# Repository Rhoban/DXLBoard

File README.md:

# Rhoban DXL Board

This communication board was designed and used by the Rhoban teams for
humanoid robots. It features:

* 3 separate dynamixel buses that can be used in parallel, compatible with
  both 3-pin and 4-pin
* A socket for a GY-85 IMU
* A socket for a Maple Mini controller (based on the Cortex-M3, 32 bit
  arm at 72Mhz)
* USB cable can be directly soldered on it
* GPIO that can be used for buttons or any other purposes

## Documentation

Here you can find documentation about:

* [Electronics](/electronics/#electronics)
* [Mechanics](/mechanics/#mechanics)
* [Firmware](/firmware/#firmware)

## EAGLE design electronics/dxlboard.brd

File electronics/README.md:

# Electronics

Here you'll find the schematic and (auto)routed board. You will need Eagle
to open the `.sch` and `.brd` files.

## Components

Here is a list of required components to build the board

Name               | Farnell ID | Quantity | Description
-------------------|------------|----------|--------------
2212S-20SG-85      | 1593469    | 2        | 1x20 0.1" female sockets for the Maple Mini
2212S-08SG-85      | 1593463    | 1        | 1x8 0.1" female socket for the IMU
MOLEX 22-03-5045   | 1104204    | 3        | Dynamixel 4 pins connector
MOLEX 22-03-5035   | 9979620    | 3        | Dynamixel 3 pins connector
ST485              | 1564306    | 3        | Buses transciever (can be replaced with MAX485), SOIC-8
R0805 22 ohms      | 2128982    | 8        | Protection resistors
R0805 1.5 Kohms    | 2129125    | 1        | USB detection resistor
R0805 2 Kohms      | 2129135    | 3        | Pull-up/Pull-down
R0805 3 Kohms      | 2129150    | 15       | Pull-up/Pull-down
C0805 100 nF       | 1759265RL  | 3        | Decoupling condensators
PMEG2005AEA        | 8737843RL  | 1        | Diode for on-board USB power supply
Maple mini      | N/A        | 1        | Controller board, featuring a 72Mhz 32-bit Cortex-M3 ARM controller
GY-85           | N/A        | 1        | 9 DOF IMU

## Powering

In the current version, the board is powered using 5V USB. You can use the mini
USB port from the Maple Mini, or solder wires to the USB part of the board (we
recommend doing that to have a better integration). There is protection diode
on the Maple Mini and on the board.

The motor power lines are connected, however the board is not designed to
handle current so you still have to build a separate hub if you want to
power servomotors. 

## Bus design

The ST485 transciever is used here for both RS485 and TTL versions. It can also
be replaced with MAX485 which is pin compatible.

22 ohms serie resistors are used for bus protections to avoid damaging transcivers from
the devices or the board in the case the bus would be driven simultaneously by both.

There is a pull-up on the A line and a the B line is pulled to 2.5V. 

When transmitting, the lines are driven by the ST485, A is the positive output and B
the negative. In this case, the A line acts exactly as the data line of a TTL device.

When receiving, if you are using only 3-pins TTL, the A line will be either 5V (for '1')
or 0V (for '0') and the B line will remain at 2.5V. In this case, the RS485 speficiation
is still respected, because A-B should be above 200mV to read a '1' and below -200mV to
read a '0'.

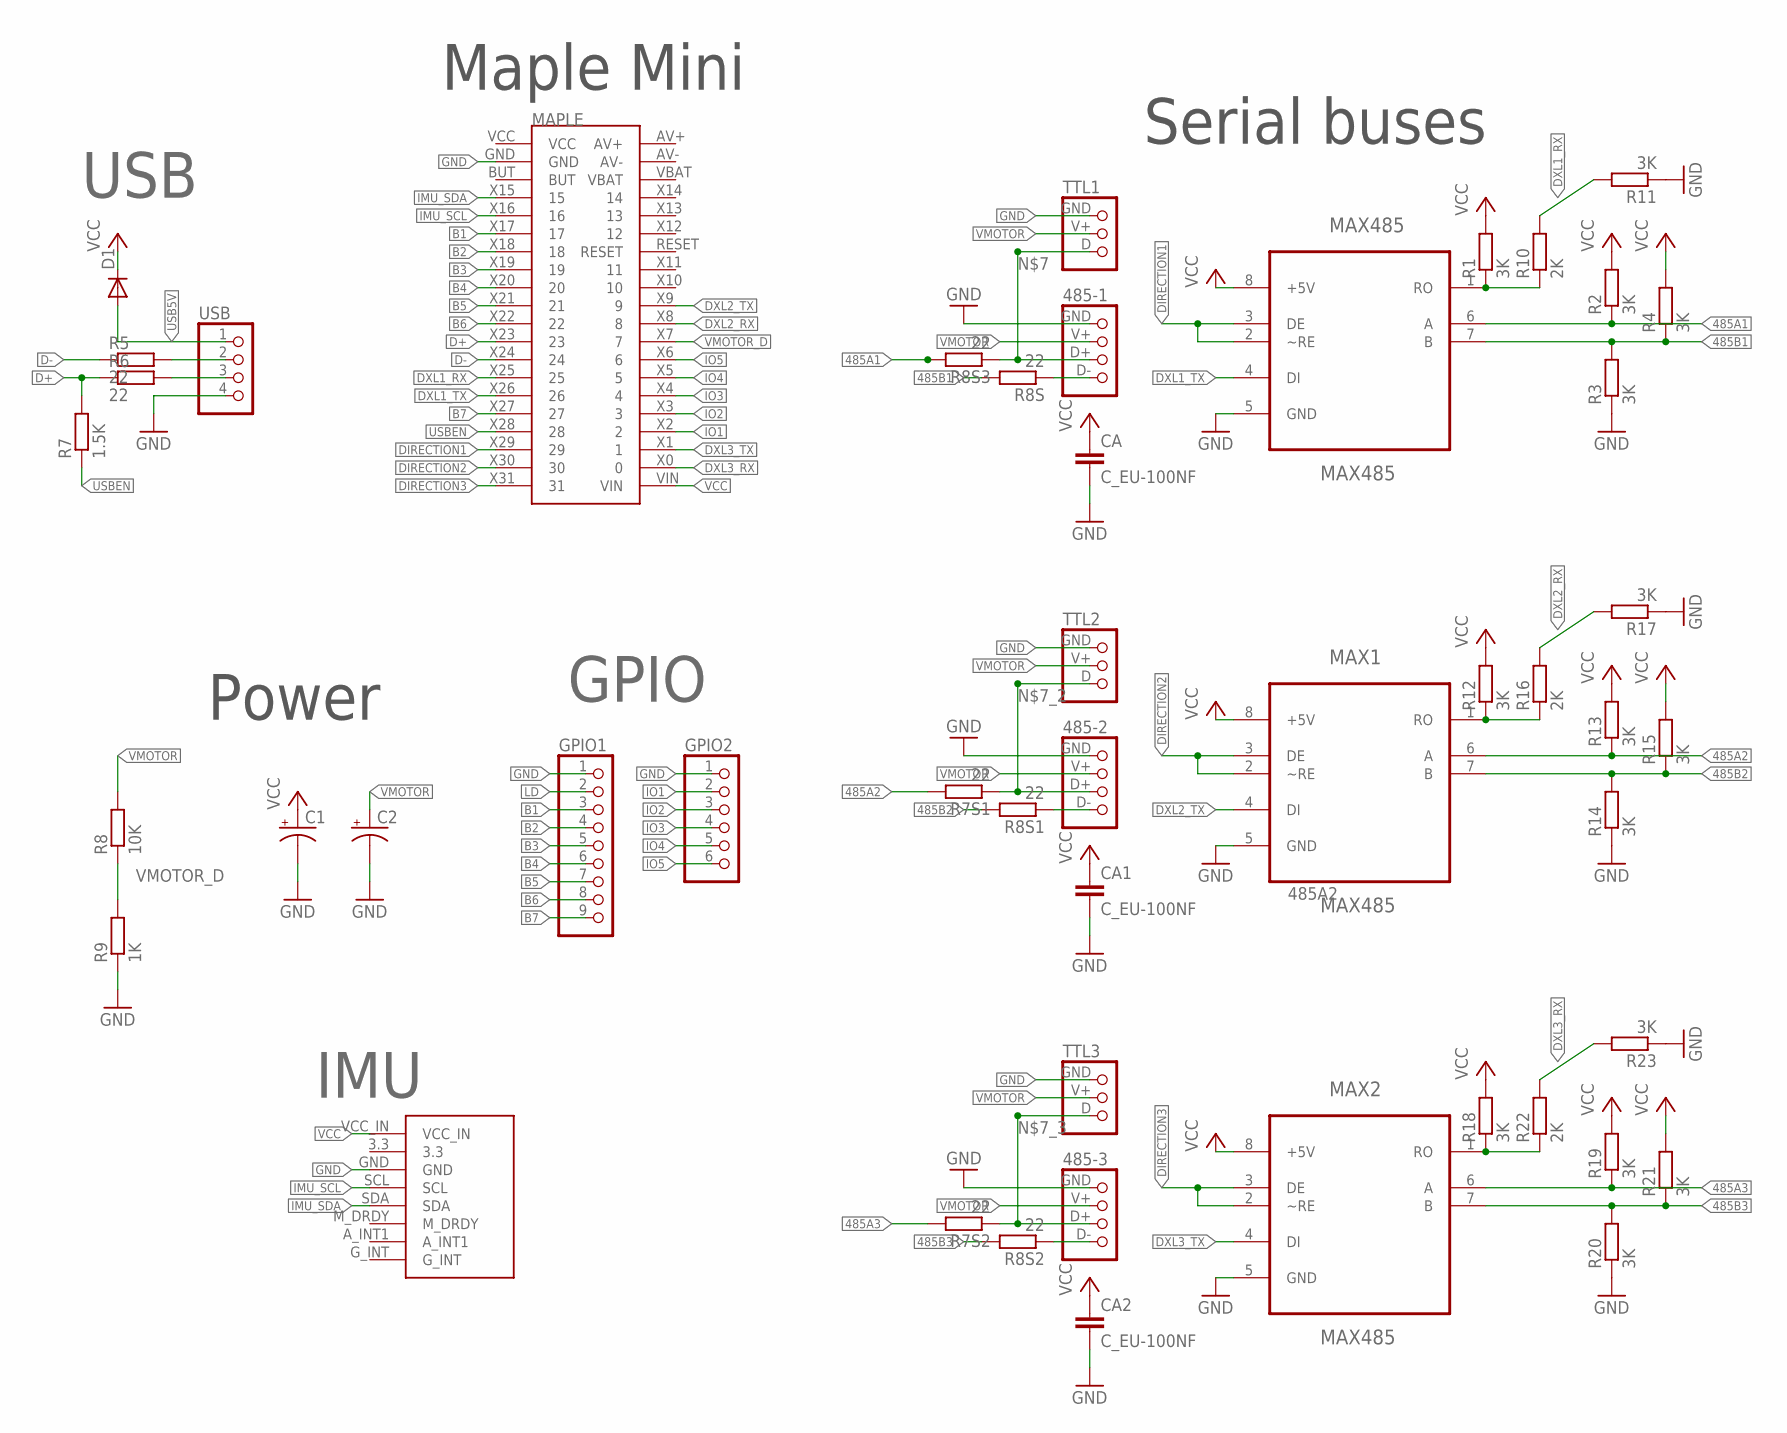
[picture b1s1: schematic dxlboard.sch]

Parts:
485-1, 485-2, 485-3: CONNEC_1X04_485; CONNEC_485; FARNELL 1104204
C1, C2: CAP_POLPTH2; CPOL-RADIAL-10UF-25V; FARNELL 1144619
CA, CA1, CA2: C_EU-100NF; C0805; FARNELL 2688486RL
D1: DIODESOD; SOD-323; FARNELL 8737843RL
GPIO1: CONNEC_1X09
GPIO2: CONNEC_1X06
MAPLE: MAPLE_MINI; CONNEC_2X20; FARNELL 1593469,1593469
MAX1, MAX2, MAX485: MAX485; SO8; FARNELL 1564306
R1, R2, R3, R4, R11, R12, R13, R14, R15, R17, R18, R19, R20, R21, R23: 3K; R0805; FARNELL 2074431
R5, R6, R7S1, R7S2, R8S, R8S1, R8S2, R8S3: 22; R0805; FARNELL 2446926
R7: 1.5K; R0805; FARNELL 2447592
R8: 10K; R0805; FARNELL 2074334RL
R9: 1K; R0805; FARNELL 2074332RL
R10, R16, R22: 2K; R0805; FARNELL 2447622
TTL1, TTL2, TTL3: CONNEC_1X03_TTL; CONNEC_TTL; FARNELL 9979620
U$6: GY-85; FARNELL 1593463
USB: CONNEC_1X04

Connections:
485A1: MAX485.6 (A), R2.1, R8S3.2
485A2: MAX1.6 (A), R7S1.2, R13.1
485A3: MAX2.6 (A), R7S2.2, R19.1
485B1: MAX485.7 (B), R3.2, R4.1, R8S.2
485B2: MAX1.7 (B), R8S1.2, R14.2, R15.1
485B3: MAX2.7 (B), R8S2.2, R20.2, R21.1
B1: GPIO1.3, MAPLE.X17 (17)
B2: GPIO1.4, MAPLE.X18 (18)
B3: GPIO1.5, MAPLE.X19 (19)
B4: GPIO1.6, MAPLE.X20 (20)
B5: GPIO1.7, MAPLE.X21 (21)
B6: GPIO1.8, MAPLE.X22 (22)
B7: GPIO1.9, MAPLE.X27 (27)
D+: MAPLE.X23 (23), R6.1, R7.2
D-: MAPLE.X24 (24), R5.1
DIRECTION1: MAPLE.X29 (29), MAX485.2 (~RE), MAX485.3 (DE)
DIRECTION2: MAPLE.X30 (30), MAX1.2 (~RE), MAX1.3 (DE)
DIRECTION3: MAPLE.X31 (31), MAX2.2 (~RE), MAX2.3 (DE)
DXL1_RX: MAPLE.X25 (25), R10.2, R11.2
DXL1_TX: MAPLE.X26 (26), MAX485.4 (DI)
DXL2_RX: MAPLE.X8 (8), R16.2, R17.2
DXL2_TX: MAPLE.X9 (9), MAX1.4 (DI)
DXL3_RX: MAPLE.X0 (0), R22.2, R23.2
DXL3_TX: MAPLE.X1 (1), MAX2.4 (DI)
DXL_1: MAX1.1 (RO), R12.1, R16.1
DXL_2: MAX2.1 (RO), R18.1, R22.1
DXL_485: MAX485.1 (RO), R1.1, R10.1
GND: 485-1.GND (1), 485-2.GND (1), 485-3.GND (1), C1.2 (-), C2.2 (-), CA.2, CA1.2, CA2.2, GPIO1.1, GPIO2.1, MAPLE.GND, MAX1.5 (GND), MAX2.5 (GND), MAX485.5 (GND), R3.1, R9.1, R11.1, R14.1, R17.1, R20.1, R23.1, TTL1.GND (1), TTL2.GND (1), TTL3.GND (1), U$6.GND, USB.4
IMU_SCL: MAPLE.X16 (16), U$6.SCL
IMU_SDA: MAPLE.X15 (15), U$6.SDA
IO1: GPIO2.2, MAPLE.X2 (2)
IO2: GPIO2.3, MAPLE.X3 (3)
IO3: GPIO2.4, MAPLE.X4 (4)
IO4: GPIO2.5, MAPLE.X5 (5)
IO5: GPIO2.6, MAPLE.X6 (6)
LD: GPIO1.2
unnamed: 485-2.D- (4), R8S1.1
unnamed: R6.2, USB.3
unnamed: 485-3.D- (4), R8S2.1
unnamed: 485-1.D- (4), R8S.1
unnamed: R5.2, USB.2
unnamed: 485-1.D+ (3), R8S3.1, TTL1.D (3)
unnamed: 485-2.D+ (3), R7S1.1, TTL2.D (3)
unnamed: 485-3.D+ (3), R7S2.1, TTL3.D (3)
USB5V: D1.2 (A), USB.1
USBEN: MAPLE.X28 (28), R7.1
VCC: C1.1 (+), CA.1, CA1.1, CA2.1, D1.1 (C), MAPLE.VIN, MAX1.8 (+5V), MAX2.8 (+5V), MAX485.8 (+5V), R1.2, R2.2, R4.2, R12.2, R13.2, R15.2, R18.2, R19.2, R21.2, U$6.VCC_IN
VMOTOR: 485-1.V+ (2), 485-2.V+ (2), 485-3.V+ (2), C2.1 (+), R8.2, TTL1.V+ (2), TTL2.V+ (2), TTL3.V+ (2)
VMOTOR_D: MAPLE.X7 (7), R8.1, R9.2

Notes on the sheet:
Serial buses
Power
Maple Mini
USB
GPIO
IMU

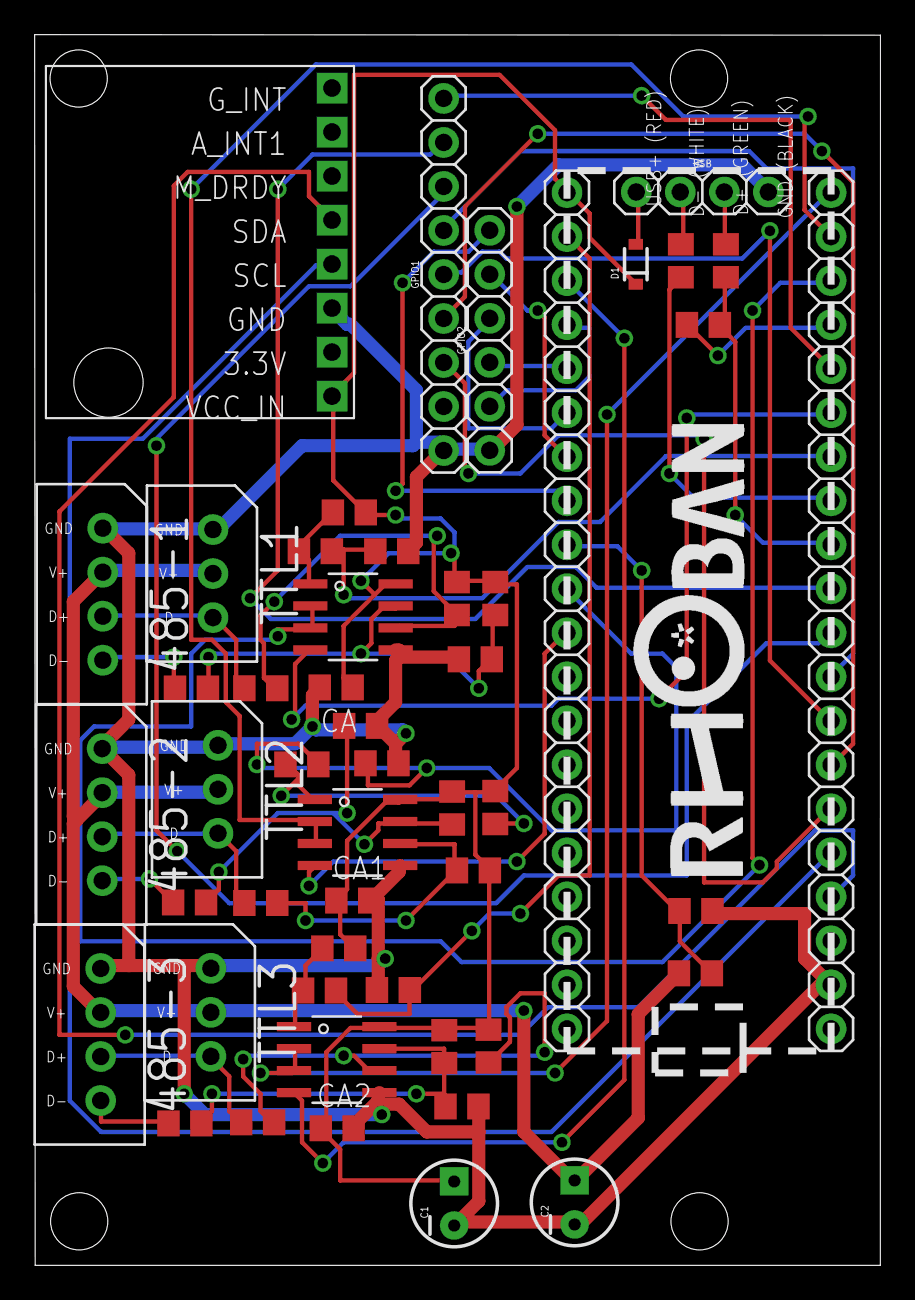
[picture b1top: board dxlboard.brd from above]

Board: 2 copper layers, 48.8 x 71.0 mm, 53 parts (0 on the bottom side), 48 nets.

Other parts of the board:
U$2, U$3, U$4, U$5: STAND-OFF

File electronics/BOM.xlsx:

|  |  | Rhoban DXLBoard BOM
Item # | *Ref Des | *Qty | Manufacturer | *Mfg Part # | Description / Value | *Package | Type | Your Instructions / Notes
1 | R1, R11, R12, R13, R14, R15, R17, R18, R19, R2, R20, R21, R23, R3, R4 | 15 | MULTICOMP | MCSR08X3001FTL | Resistor 3K | 0805 | SMD | Farnell : 2074431
2 | R5, R6, R7S1, R7S2, R8S, R8S1, R8S2, R8S3 | 8 | MULTICOMP | MCWR08X22R0FTL | Resistor 22 Ohms | 0805 | SMD | Farnell : 2446926
3 | R7 | 15 | MULTICOMP | MCWR08X1501FTL | Resistor 1.5K | 0805 | SMD | Farnell : 2447592
4 | R10, R16, R22 | 3 | MULTICOMP | MCWR08X2001FTL | Resistor 2K | 0805 | SMD | Farnell : 2447622
5 | R8 | 1 | MULTICOMP | MCSR08X1002FTL | Resistor 10K | 0805 | SMD | Farnell : 2074334RL
6 | R9 | 1 | MULTICOMP | MCSR08X1001FTL | Resistor 1K | 0805 | SMD | Farnell : 2074332RL
7 | CA, CA1, CA2 | 3 | MURATA | GCM21BR72A104KA37K | Capacitor 100nF | 0805 | SMD | Farnell : 2688486RL
8 | C1, C2 | 2 | RUBYCON | 25YXF47MEFC5X11 | Capacitor 47uF | Radial 5mm | Thru-Hole | Farnell : 1144619
9 | D1 | 1 | NEXPERIA | PMEG2005AEA | Diode Schottky | SOD-323 | SMD | Farnell : 8737843RL
10 | 485-1, 485-2, 485-3 | 3 | MOLEX | 22-03-5045 | Connector 4 pins | - | Thru-Hole | Farnell : 1104204
11 | TTL1, TTL2, TTL3 | 3 | MOLEX | 22-03-5035 | Connector 3 pins | - | Thru-Hole | Farnell : 9979620
12 | MAX1, MAX2, MAX485 | 3 | STMICROELECTRONICS | ST485BDR | Transceiver RS485 | SOIC8 | SMD | Farnell : 1564306
13 | U$6 | 1 | MULTICOMP | 2212S-08SG-85 | 0.1’’ female header, 8 pins | - | Thru-Hole | Farnell : 1593463
14 | MAPLE | 2 | MULTICOMP | 2212S-20SG-85 | 0.1’’ female header, 20 pins | - | Thru-Hole | Farnell : 1593469
Click for Instructions on How to Create a BOM

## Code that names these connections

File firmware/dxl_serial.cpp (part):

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#include "dxl_serial.h"

// Serial com
#define DIRECTION1      29
#define DIRECTION2      30
#define DIRECTION3      31

// Devices allocation
static bool serialInitialized = false;
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
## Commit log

2017-05-31 README
2017-05-31 Electronics
2017-05-31 READMEs
2017-05-31 Boards
2017-05-31 ST485 qty
2017-05-31 Mechanics
2017-05-31 Fixing dimensions img
2017-05-31 Git ignore file
2017-05-31 Firmware
2017-05-31 detail
2017-05-31 anchors
2017-05-31 Removing unused
2017-05-31 Removing useless
2017-06-05 GY85 doc
2017-06-05 Bytes
2017-06-05 IMU ID
2017-06-15 Missing important part of code during port to open source repo
2017-10-04 Details
2017-12-14 changing to protocoll 2. removing artificial sync read
2017-12-14 fixed compiling errors
2017-12-15 fixed memory bug. added some prints for debug
2017-12-15 merged code from other rhoban git for protocol 2
2017-12-19 fixing bugs in new protocol. IMU works now
2017-12-19 just formating
2017-12-21 default bootloader to maple
2018-01-11 board is working, only splitting for the 3 serial busses is missing
2018-01-11 working on sync package splitting
2018-01-12 reading with multiple motors works now
2018-01-16 sorting of sync read returns works now
2018-01-22 perf increases
2018-01-23 working on performance
2018-01-24 implemented super sync
2018-01-24 testing to ignore crc of status packages for performance
2018-01-24 direktly sending all bytes to usb
2018-01-25 increased performance by direct transfer of bytes from the slaves
2018-02-01 clean up. changed IMU to 200hz and disabled magnetometer
2018-02-05 Adding Farnell attributes
2018-03-10 Errors check in gy85
2018-08-30 Switching labels to XRef
2018-08-30 Updating FARNELL attributes & making BOM
2018-08-30 Fixing item #
2018-10-29 gerber files
2018-10-29 Gerber
2018-10-29 smt th
2018-10-29 Adding centroid
2018-10-29 centroid txt
2019-04-04 small fix for ping response
2019-04-04 changed IMU configuration for higher update rate and larger range of acceleration
2019-05-01 added warning in readme

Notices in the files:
parts and their libraries:
SparkFun-Electromechanical: Licensing: CC v3.0 Share-Alike You are welcome to use this library for commercial purposes.
